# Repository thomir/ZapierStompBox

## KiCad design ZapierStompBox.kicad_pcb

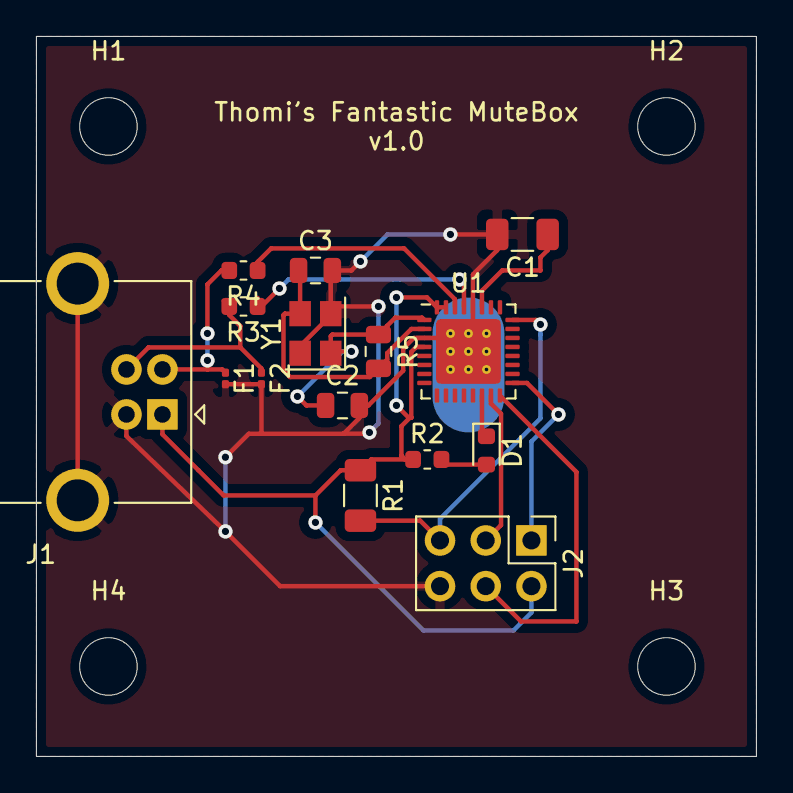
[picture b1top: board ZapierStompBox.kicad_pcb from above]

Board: 2 copper layers, 40.0 x 40.0 mm, 19 parts (0 on the bottom side), 15 nets.

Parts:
C1: 100 uF; C_1206_3216Metric
C2, C3: 22pF; C_0805_2012Metric
D1: LED; LED_0603_1608Metric
F1, F2: Polyfuse; Fuse_0201_0603Metric
H1, H2, H3, H4: MountingHole; MountingHole_3.2mm_M3
J1: USB_B; USB_B_OST_USB-B1HSxx_Horizontal
J2: AVR-ISP-6; PinHeader_2x03_P2.54mm_Vertical
R1: 10k; R_1206_3216Metric
R2: 1k; R_0603_1608Metric
R3, R4: 22R; R_0603_1608Metric
R5: 1M; R_0805_2012Metric
U1: ATmega16U2-AU; QFN-32-1EP_5x5mm_P0.5mm_EP3.6x3.6mm_ThermalVias
Y1: 16Mhz; Crystal_SMD_3225-4Pin_3.2x2.5mm

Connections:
GND: C1.2, C2.2, C3.2, F1.2, F2.2, J1.4, J1.5, J2.6, U1.3, U1.28, Y1.2, Y1.4
unnamed: C1.1, U1.27
unnamed: C2.1, R5.1, U1.1, Y1.1
unnamed: C3.1, R5.2, U1.2, Y1.3
unnamed: D1.1, U1.14
unnamed: D1.2, R2.2
unnamed: F1.1, J1.2, R4.2
unnamed: F2.1, J1.3, R3.2
unnamed: J2.1, U1.17
unnamed: J2.3, U1.15
unnamed: J2.4, U1.16
unnamed: J2.5, R1.2, U1.24
unnamed: R3.1, U1.29
unnamed: R4.1, U1.30
VCC: J1.1, J2.2, R1.1, R2.1, U1.4, U1.31, U1.32

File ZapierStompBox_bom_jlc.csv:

"Comment","Designator","Footprint","LCSC Part #"
"100 uF","C1","C_1206_3216Metric","C15008"
"22pF","C2,C3","C_0805_2012Metric","C1804"
"LED","D1","LED_0603_1608Metric","C72038"
"Polyfuse","F2,F1","Fuse_0201_0603Metric","C10677"
"10k","R1","R_1206_3216Metric","C17902"
"1k","R2","R_0603_1608Metric","C21190"
"22R","R3,R4","R_0603_1608Metric","C23345"
"1M","R5","R_0805_2012Metric","C17514"
"ATmega16U2-AU","U1","QFN-32-1EP_5x5mm_P0.5mm_EP3.6x3.6mm_ThermalVias","C17317"
"16Mhz","Y1","Crystal_SMD_3225-4Pin_3.2x2.5mm","C13738"

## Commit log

2020-04-17 initial commit.
2020-04-17 Update jlcpcb part number for uC
2020-04-17 Fix package for uC, re-work component placement.
2020-04-19 Some component changes.
